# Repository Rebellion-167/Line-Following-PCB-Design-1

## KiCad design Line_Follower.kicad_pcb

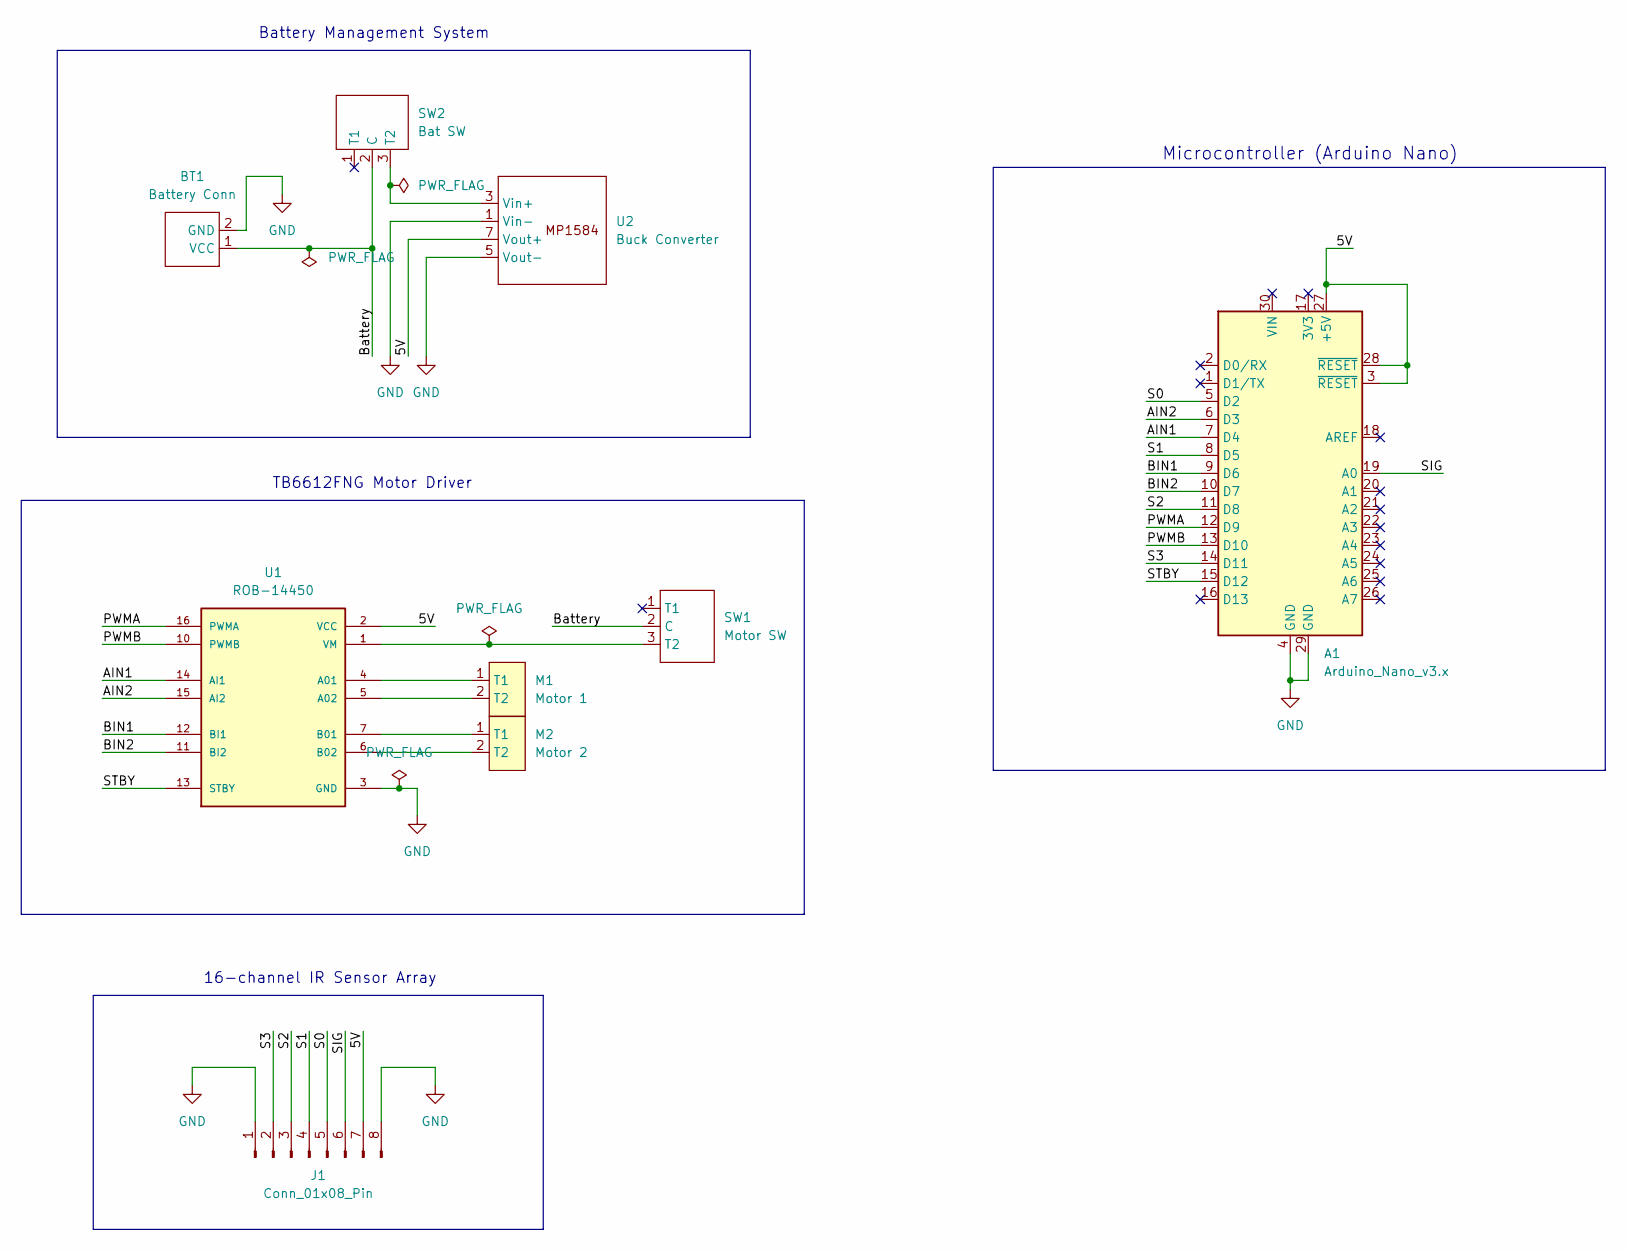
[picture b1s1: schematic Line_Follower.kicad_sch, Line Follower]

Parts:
A1: Arduino_Nano_v3.x; Arduino_Nano
BT1: Battery Conn; TerminalBlock_MetzConnect_Type101_RT01602HBWC_1x02_P5.08mm_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
J1: Conn_01x08_Pin; PinHeader_1x08_P2.54mm_Vertical
M1: Motor 1; TerminalBlock_MetzConnect_Type101_RT01602HBWC_1x02_P5.08mm_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
M2: Motor 2; TerminalBlock_MetzConnect_Type101_RT01602HBWC_1x02_P5.08mm_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
SW1: Motor SW; SW_Slide_SPDT_Straight_CK_OS102011MS2Q
SW2: Bat SW; SW_Slide_SPDT_Straight_CK_OS102011MS2Q
U1: ROB-14450; MODULE_ROB-14450; PARTREV 11-13-17
U2: Buck Converter; DC-BRICK

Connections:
/5V: A1.3 (~RESET), A1.27 (+5V), A1.28 (~RESET), J1.7, U1.2 (VCC), U2.7 (Vout+)
/AIN1: A1.7 (D4), U1.14 (AI1)
/AIN2: A1.6 (D3), U1.15 (AI2)
/BIN1: A1.9 (D6), U1.12 (BI1)
/BIN2: A1.10 (D7), U1.11 (BI2)
/Battery: BT1.1 (VCC), SW1.2 (C), SW2.2 (C)
/PWMA: A1.12 (D9), U1.16 (PWMA)
/PWMB: A1.13 (D10), U1.10 (PWMB)
/S0: A1.5 (D2), J1.5
/S1: A1.8 (D5), J1.4
/S2: A1.11 (D8), J1.3
/S3: A1.14 (D11), J1.2
/SIG: A1.19 (A0), J1.6
/STBY: A1.15 (D12), U1.13 (STBY)
GND: A1.4 (GND), A1.29 (GND), BT1.2 (GND), J1.1, J1.8, U1.3 (GND), U1.8 (GND), U1.9 (GND), U2.1 (Vin-), U2.5 (Vout-)
unnamed: M1.1 (T1), U1.4 (A01)
unnamed: M1.2 (T2), U1.5 (A02)
unnamed: M2.1 (T1), U1.7 (B01)
unnamed: M2.2 (T2), U1.6 (B02)
unnamed: SW1.3 (T2), U1.1 (VM)
unnamed: SW2.3 (T2), U2.3 (Vin+)

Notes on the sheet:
Microcontroller (Arduino Nano)
16-channel IR Sensor Array
Battery Management System
TB6612FNG Motor Driver

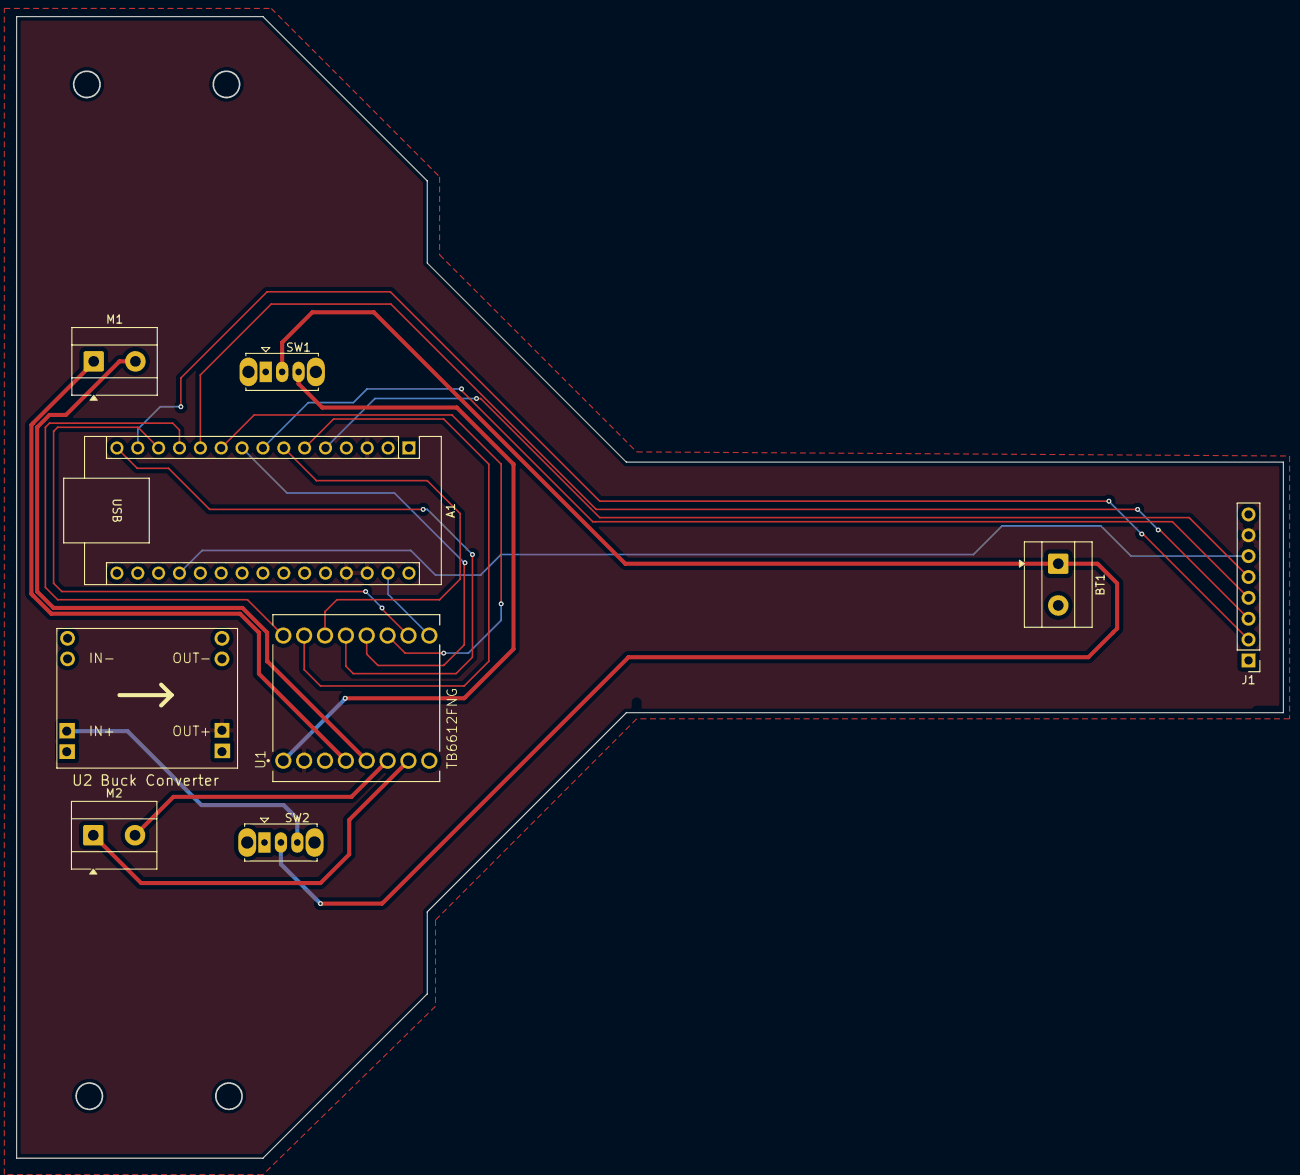
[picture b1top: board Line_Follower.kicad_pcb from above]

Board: 2 copper layers, 154.2 x 139.0 mm, 9 parts (0 on the bottom side), 21 nets.

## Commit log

2026-04-13 Main Project File
2026-04-13 Schematic File
2026-04-13 PCB Design File
2026-04-13 Local Project Settings
2026-04-15 Symbols and Footprints used
2026-04-15 Gerbers and Drill Files
2026-04-15 Schematic and PCB final design
